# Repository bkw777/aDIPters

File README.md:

# aDIPters
This is a collection of different adapter PCBs to plug SMT parts into DIP sockets, and/or to use a writable part in place of an originally read-only part.
Generally to use a newer PLCC, SOIC, or TSOP EEPROM or Flash part to replace a DIP mask ROM or UV EPROM in a vintage computer.

Most of the PCBs have holes that are intentionally too small to use standard pin headers for the DIP legs.  
Here is how to do the legs: https://gist.github.com/bkw777/52d85d89eeff8445cc667685d05ea94d  
It's less convenient than generic pin headers but the point is for the legs to be as thin as the DIP legs they are emulating so as not to damage sockets, and to have the replacement "chip" be low profile without the big isulator & shoulder block taking up space so the replacement chip fits in more places.  

## 28C256_to_27C256

http://tandy.wiki/28C256_to_27C256

Use an electrically re-programmable EEPROM (28C256) in any socket that normally takes a 256K x 8 UV EPROM (27C256) or standard pinout mask ROM.

The chip may be (re)programmed after soldering by setting the jumpers for programming and placing the board directly in a programmer.

## FlexROM_100

info: http://tandy.wiki/FlexROM_100  

PCB: https://www.pcbway.com/project/shareproject/FlexROM_100.html  
BOM: https://www.digikey.com/short/mmz0bp0h

Uses an electrically re-programmable EEPROM (28C256) in place of the non-standard pinout mask ROM (LH535618) in a TRS-80 Model 100 system rom socket.

Includes /CS signal send-return breakout to use with [REX main rom feature](http://bitchin100.com/wiki/index.php?title=Main_ROM_Management_Feature). This allows not only using the REX main-rom feature but also allows reverting from REX back to the internal main rom without opening the case again to re-install the original main rom chip. It is especially convenient with this [updated PCB for REX Classic](http://tandy.wiki/Building_a_REX), which allows using removable female dupont jumper wires between the FlexROM_100 inside the computer and the REX in the option rom compartment.

To program the eeprom, use either the FlexROM_100_programming_adapter below, or an SOIC-28 test clip.

To install without REX, just install a jumper on the /CS pins.

To use the REX main rom feature:  
* Run 2 10-inch female dupont jumper wires from the /CS pins out to the option-rom compartment.  
* Label the /CS_BUS wire so that you can tell which one it is after the machine is re-assembled.  
* Attach the /CS_BUS wire to TP1 on the REX.  
* Leave the /CS_IC wire un-connected loose in the option rom compartment. Do NOT connect it to TP2. This wire is only used if/when you want to revert from the REX back to the internal main rom without opening the case again.

To re-enable the internal ROM (To remove the REX, or just to stop using the main-rom feature):  
* Disconnect the /CS_BUS wire from the REX TP1 pin.  
* Connect the /CS_BUS wire to the /CS_IC wire with a short male dupont jumper wire.

## FlexROM_100 Programming Adapter

Allows programming the FlexROM_100 without an SOIC-28 test clip.  

## FlashROM_100
Same as FlexROM_100 but using a 29F010 or compatible flash part instead of a 28C256 EEPROM part.  
The board uses a 128K FLASH chip simply because they are what's available these days.  
28C256 have gone from $5 each to $15 each in the last few years.

To program the chip, use the [FlashROM_100_Programming_Adapter](#flashrom_100-programming-adapter) below, and tell the programmer to ignore the size discrepency.  
Example, using a TL-866 and the [minipro](https://gitlab.com/DavidGriffith/minipro) app:  
```
$ minipro -p "SST39SF010A" -u -P -s -w Model_100.y2k.bin
Found TL866II+ 04.2.132 (0x284)
Warning: Firmware is newer than expected.
  Expected  04.2.131 (0x283)
  Found     04.2.132 (0x284)
Chip ID: 0xBFB5  OK
Warning: Incorrect file size: 32768 (needed 131072)
Erasing... 0.40Sec OK
Writing Code...  1.64Sec  OK
Reading Code...  0.25Sec  OK
Verification OK
$
```

TIP: You can run the Model 102 main rom on a Model 100 machine. It fixes a few obscure bugs and there are some tiny differences in the screen font, but otherwise works identically and is compatible with all of the hardware and software.  

There are 2 versions, PLCC and TSOP

### PLCC

https://www.pcbway.com/project/shareproject/FlashROM_100.html

### TSOP

PCB: https://www.pcbway.com/project/shareproject/FlashROM_100_tsop.html  
BOM: https://www.digikey.com/short/7798tt51

## FlashROM_100 Programming Adapter

PCB: https://www.pcbway.com/project/shareproject/Programming_Adapter_for_FlashROM_100.html

Allows re-writing the FlashROM_100.

## FlexROM_102

http://tandy.wiki/FlexROM_102

([DigiKey cart](https://www.digikey.com/en/mylists/list/5FEBN35SNT)) Built 2025.01.15 by John Hutchison KI5NYZ

([OshPark PCB](https://oshpark.com/shared_projects/NmfnbreW)) Built 2025.01.15 by John Hutchison KI5NYZ

This is a cross between the 28C256_to_27C256 above, and the FlexROM_100 above.
This is like FlexROM_100 above but for TANDY 102, 200, and some late-model 100's.

TANDY 102, 200, and some late-model TRS-80 Model 100's have a standard pinout main rom, and so to replace the main rom you can use a plain 27C256, or the generic 28C256_to_27C256 above, or FlexROM_102.  
If a Model 100 has a main rom with part number LH535618, it requires FlexROM_100.  
If a Model 100 has a main rom with part number 3256C07, it requires FlexROM_102 (or 28C256_to_27C256 or an ordinary 27C256).

This just adds pins to break out /CS for use with the main-rom feature of REX Classic, the same as FlexROM_100 above.

The Model 102 system ROM is soldered, so this requires de-soldering the original chip and installing a DIP-28 socket also.

To program the chip, it's like 28C256_to_27C256 above.
Install a jumper on the /CS pins, set the mini jumpers to PROGRAM (two shunts on the two pairs of pins), put the board directly in the programmer, and set the programmer for 28C256.  
There is no separate programming adapter needed like for FlexROM_100 and FlashROM_100.

To install/run, install a jumper on the /CS pins, set the mini jumpers to RUN (single shunt on the two center pins), and install the board in the Model 102 in place of the main rom.

There is a jumper on the /CS pins in both cases. The only time there is not a jumper on the /CS pins is to use the REX Classic main-rom feature.  
See the FlexROM_100 directions for that.

Some late-model TRS-80 Model 100\'s  

## FlexROM_200_M13
THIS ONE IS UNTESTED  
Replaces the 8K ROM at position M13 in TANDY 200

[FlexROM_200_M13 BOM](FlexROM_200_M13.BOM.csv) or ([DigiKey cart](https://www.digikey.com/short/q3zm9cf4))  
http://tandy.wiki/FlexROM_200

## FLASH_23C1000

http://tandy.wiki/FLASH_23C1000  
https://www.pcbway.com/project/shareproject/FlashROM_8300.html

Replaces 23C1000, uPD23C1000, D23C1000A, MX23C1000, etc.

This board accepts a variety of writable flash, eeprom, or eprom devices to replace the non-standard pinout 23C1000.
Tested on NEC PC-8300, PC-8401 Starlet, and PC-8500. Not tested but should also work in Cambridge Z88, or anywhere a 23C1000 is used.

The nominal flash chip is SST39SF010, but there are several other compatible parts. The specs for a compatible chip are:
* 128K x 8  
* 5v  
* parallel  
* 7x9pin PLCC32, or 8x14mm sTSOP32, or 8x20mm TSOP32  

It also supports EPROM and EEPROM parts as well as flash parts.  
At least the following parts are compatible:  
* 29F010  
* 39SF010  
* 29SF010  
* 29EE010  
* 28C010  
* 28F010  
* 27SF010  
* 27C010  

The R3 resistor is only needed for EPROM and EEPROM devices that have a Vpp pin (27xxx/28xxx). Flash devices (29xxx) don't use it.

The RUN/PRG jumper alters the pinout, so that the chip may be programmed by placing the board directly in a programmer.

For programming:  
1. Place the jumper in the PRG position  
1. Place the board in the programmer  

For installing in place of the 23C1000:  
1. Place the jumper in the RUN position  
1. Place the board in the socket with the top 4 pins (1, 2, 31, 32) hanging off the pin #1 end of the socket, and the bottom 28 pins 3-30 filling the socket. Board pin 3 ends up in socket pin 1.

For NEC PC-8401, cut pin 1 a little short so that it doesn't touch R65, or use the DIP-28 version of this board below instead of this DIP-32 version.

For safety, cut all 4 top pins a little short, 1, 2, 31, 32, so that they don't risk touching the motherboard.  
These pins are only used for programming. They only need to be long enough for the programmer socket to grab them for a few seconds.

## FLASH_23C1000_DIP28

http://tandy.wiki/FLASH_23C1000  
https://www.pcbway.com/project/shareproject/FLASH_23C1000_DIP28.html

Replaces 23C1000, uPD23C1000, D23C1000A, MX23C1000, etc.

Same as FLASH_23C1000, except:
* Does not exceed the original parts DIP-28 footprint.  
* Does not accept 27C010 or other parts that have a Vpp pin.  
* Does accept 256k *020 parts.  

Tested in NEC PC-8300, PC-8401, PC-8500  
Not yet tested but should also work in Cambridge Z88

Programming this version is slightly more complicated.

To program:  
* Place the board in the programmer 2 rows from the top, such that pin 1 on the board is in pin 3 of an imaginary DIP-32 in the programmer.
* Remove the VCC-/WE jumper.
* Move the /OE-A16 jumper to /OE
* Connect the A16 pin to programmer DIP-32 pin 2 using a female-to-male dupont jumper wire
* Connect the VCC pin to programmer DIP-32 pin 32
* Connect the /WE pin to programmer DIP-32 pin 31

Configure the programmer for whatever device is installed on the board, IE SST39SF010A etc.

To install:  
* Install a jumper across the VCC-/WE pins
* Move the /OE-A16 jumper to A16
* Install the board in the DIP-28 socket in place of any uPD23C1000, D23C1000A, MX23C1000 etc.

## TANDY 100/102/200 Option ROM to 27C256 pinout programming adapter

If you have a Molex 8878-28S socket, this provides a pinout adapter for the non-standard TANDY pinout to a standard 27C256 pinout to allow reading Model 100/200 Option ROMs in an eprom programmer without having to bend the pins or desolder the chip.  
The sockets haven't been made for decades, but sometimes they turn up on [ebay](ebay.com/sch/?_nkw=molex%208878-28S) and other places.  
Search terms: The socket is physically marked "Molex 8878-28S".  
The [datasheet](datasheets/015299282_sd_corrected.pdf) says the part number is 78805-0518 or 15-29-9282.  

The jumpers provide 5 different ways to handle pin #23 in the socket.  

In the Model 100 option rom socket, pin 23 is connected to the ALE bus signal and labelled as a 2nd active-low /CE.  
To make the Molex socket on the adapter emulate the option rom socket in a Model 100 as completely as possible, pin 23 in the socket should be a 2nd copy of the /CE pin from the programmer. Basically using the /CE signal as a fake ALE signal.  
But only 2 known option roms actually use the signal, MS MultiPLAN and Interactive Solutions.  
Most commercial option roms are a 27C256 in some form of pinout adapter, and they don't connect the ALE pin from the bus to anything.  

The jumpers allow pin 23 in the Molex socket to be connected to the programmer pins: GND, VCC, VPP, /CE, or nothing.  
* For the molded plastic roms with LH53562x part numbers (MS MultiPLAN, Ineractive Solutions), use the /CE position.  
* For most 3rd party roms constructed of a ceramic 27C256 with a pinout adapter, use either /CE, or remove the jumper entirely.  
* The other options are for possible future use with other new custom option rom modules like [Teeprom](httpsgithub.com/bkw777/Teeprom) or [M4ROM](https://github.com/bkw777/M4ROM/) etc, that might be specifically designed to use that otherwise un-used pin for VPP or /WE etc. Currently no such modules are wired like that, so generally just leave it on /CE.

## DS1000

## SM8 SSOP-8 DIP-8

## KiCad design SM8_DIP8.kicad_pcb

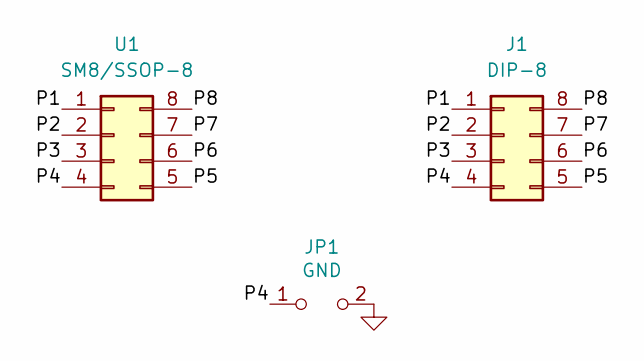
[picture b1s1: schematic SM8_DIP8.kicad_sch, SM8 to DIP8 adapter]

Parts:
J1: DIP-8; DIP8_0.3_pcb_sil_pins
JP1: GND; SolderJumper-2_P1.3mm_Open_RoundedPad1.0x1.5mm
U1: SM8/SSOP-8; SSOP-8_2.95x2.8x0.65

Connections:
/P1: J1.1, U1.1
/P2: J1.2, U1.2
/P3: J1.3, U1.3
/P4: J1.4, JP1.1 (A), U1.4
/P5: J1.5, U1.5
/P6: J1.6, U1.6
/P7: J1.7, U1.7
/P8: J1.8, U1.8
GND: JP1.2 (B)

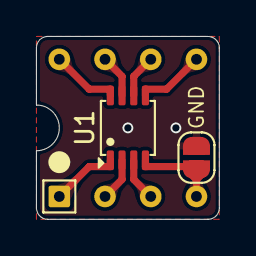
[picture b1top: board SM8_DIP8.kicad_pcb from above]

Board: 2 copper layers, 10.2 x 10.2 mm, 3 parts (0 on the bottom side), 8 nets.

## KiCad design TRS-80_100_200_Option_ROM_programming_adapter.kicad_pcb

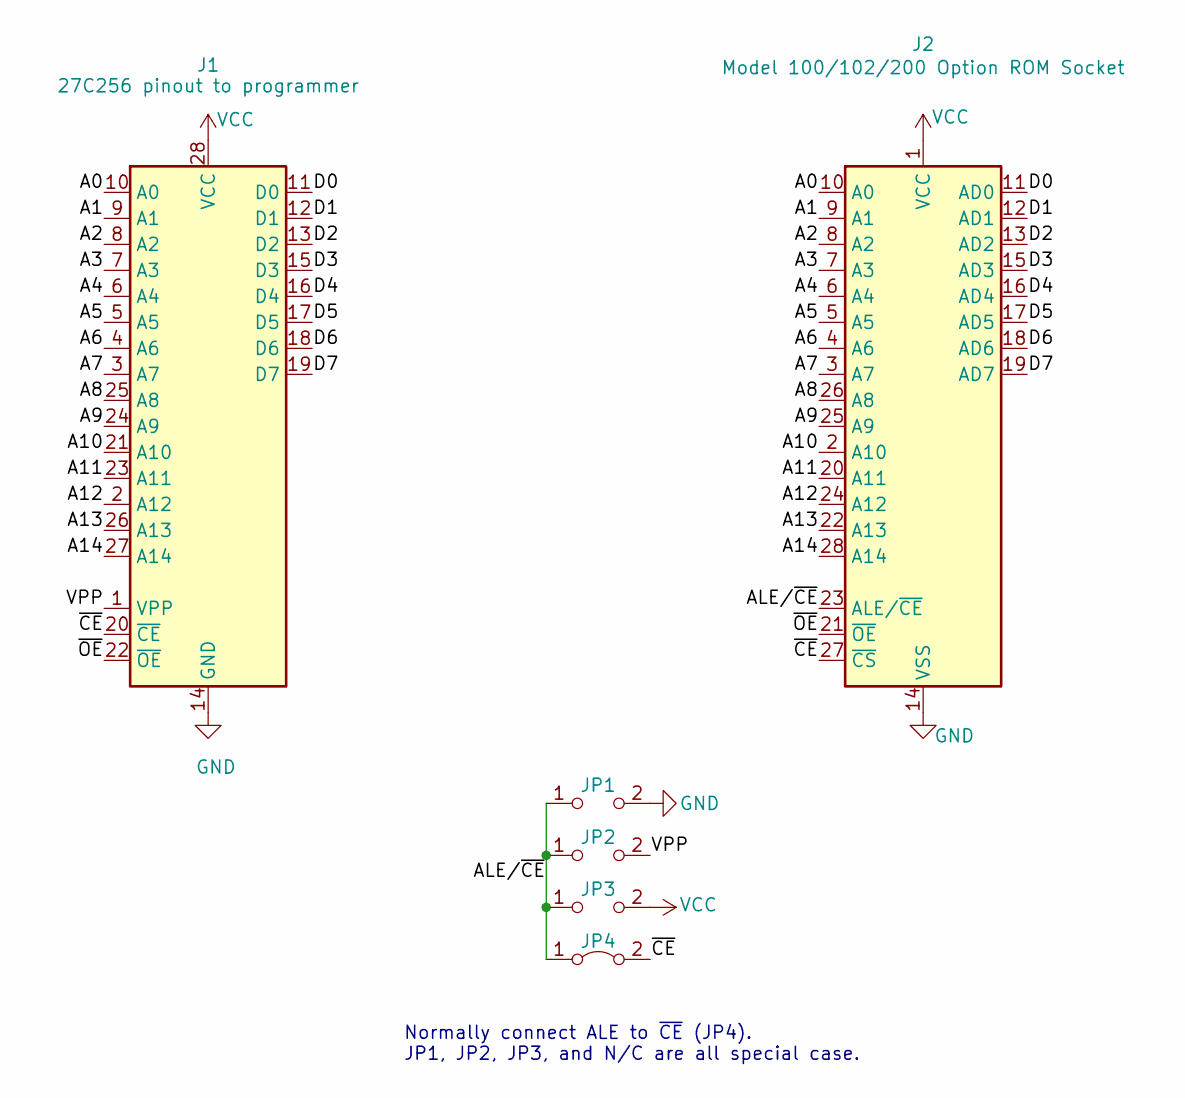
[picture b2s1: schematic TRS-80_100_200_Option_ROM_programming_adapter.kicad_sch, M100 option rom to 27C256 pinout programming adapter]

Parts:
J1: 27C256 pinout to programmer; 2x28_0.3_0.1_pins
J2: Model 100/102/200 Option ROM Socket; Molex_78805
JP1: GND; PinHeader_1x02_P2.54mm_Vertical
JP2: VPP; PinHeader_1x02_P2.54mm_Vertical
JP3: VCC; PinHeader_1x02_P2.54mm_Vertical
JP4: ~{CE}; PinHeader_1x02_P2.54mm_Vertical_shorted

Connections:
/A0: J1.10 (A0), J2.10 (A0)
/A1: J1.9 (A1), J2.9 (A1)
/A2: J1.8 (A2), J2.8 (A2)
/A3: J1.7 (A3), J2.7 (A3)
/A4: J1.6 (A4), J2.6 (A4)
/A5: J1.5 (A5), J2.5 (A5)
/A6: J1.4 (A6), J2.4 (A6)
/A7: J1.3 (A7), J2.3 (A7)
/A8: J1.25 (A8), J2.26 (A8)
/A9: J1.24 (A9), J2.25 (A9)
/A10: J1.21 (A10), J2.2 (A10)
/A11: J1.23 (A11), J2.20 (A11)
/A12: J1.2 (A12), J2.24 (A12)
/A13: J1.26 (A13), J2.22 (A13)
/A14: J1.27 (A14), J2.28 (A14)
/ALE/~CE: J2.23 (ALE/~CE), JP1.1 (A), JP2.1 (A), JP3.1 (A), JP4.1 (A)
/D0: J1.11 (D0), J2.11 (AD0)
/D1: J1.12 (D1), J2.12 (AD1)
/D2: J1.13 (D2), J2.13 (AD2)
/D3: J1.15 (D3), J2.15 (AD3)
/D4: J1.16 (D4), J2.16 (AD4)
/D5: J1.17 (D5), J2.17 (AD5)
/D6: J1.18 (D6), J2.18 (AD6)
/D7: J1.19 (D7), J2.19 (AD7)
/VPP: J1.1 (VPP), JP2.2 (B)
/~CE: J1.20 (~CE), J2.27 (~CS), JP4.2 (B)
/~OE: J1.22 (~OE), J2.21 (~OE)
GND: J1.14 (GND), J2.14 (VSS), JP1.2 (B)
VCC: J1.28 (VCC), J2.1 (VCC), JP3.2 (B)

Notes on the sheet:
Normally connect ALE to ~{CE} (JP4). JP1, JP2, JP3, and N/C are all special case.

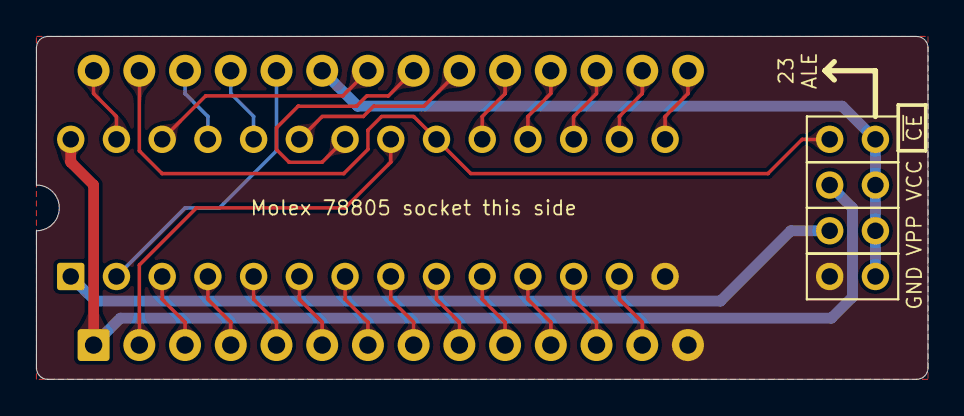
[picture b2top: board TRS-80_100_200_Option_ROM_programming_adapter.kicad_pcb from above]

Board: 2 copper layers, 49.5 x 19.1 mm, 6 parts (0 on the bottom side), 29 nets.

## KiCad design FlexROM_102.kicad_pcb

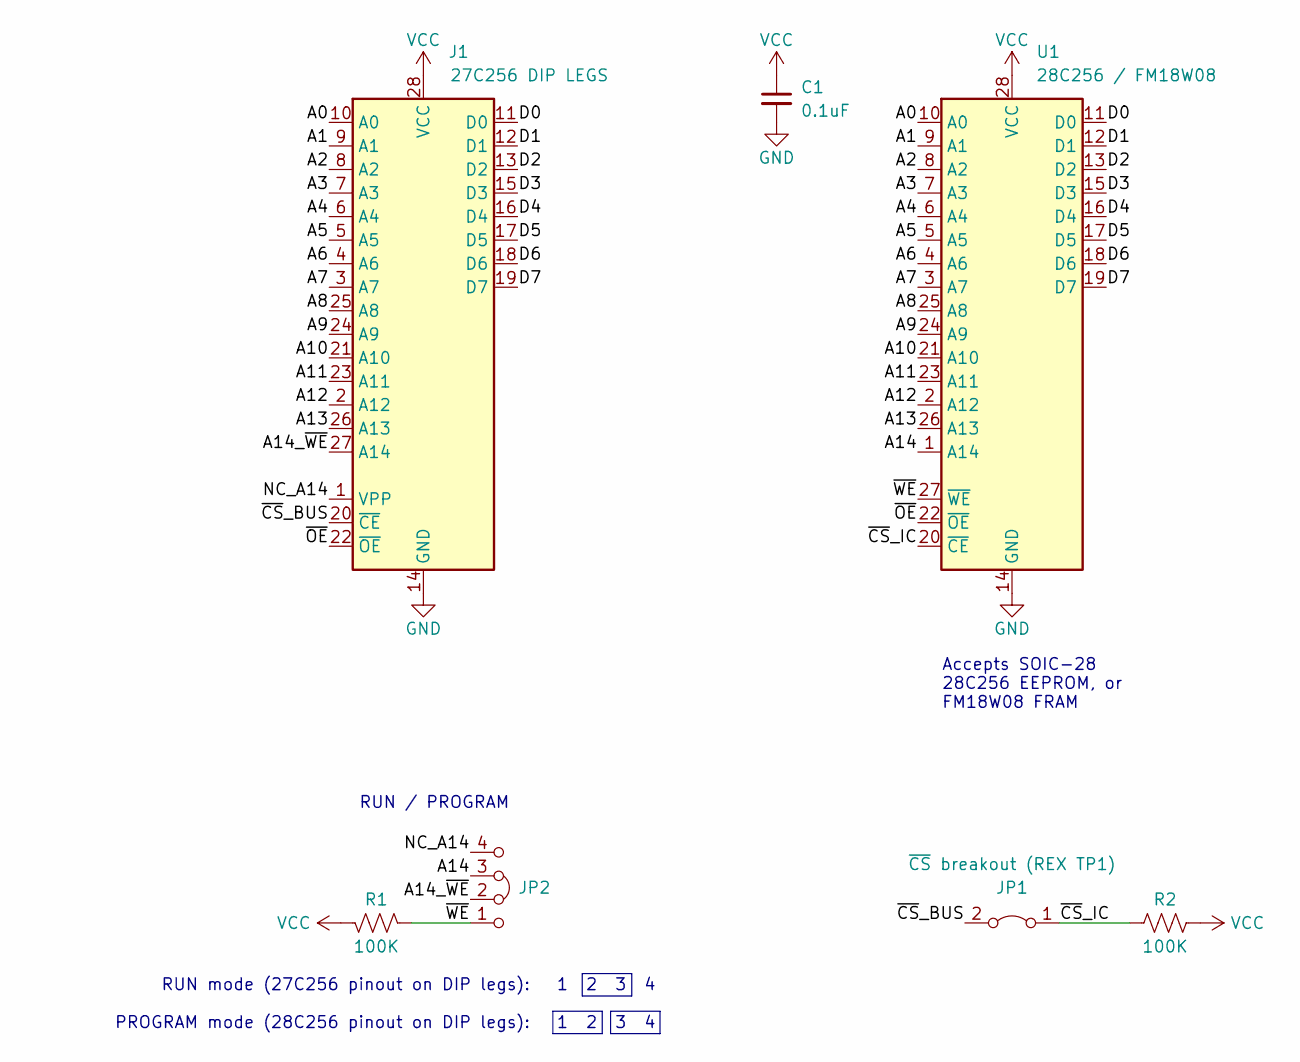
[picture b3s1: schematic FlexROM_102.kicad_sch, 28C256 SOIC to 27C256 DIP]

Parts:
C1: 0.1uF; C_0805
J1: 27C256 DIP LEGS; DIP28_0.6_pcb
JP1: ~{CS} breakout (REX TP1); Pin_Header_Angled_1x02_Pitch2.54mm
JP2: Jumper_4_Bridged23; PinHeader_1x04_P2.00mm_Horizontal
R1, R2: 100K; R_0805
U1: 28C256 / FM18W08; SOIC28W

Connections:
/A0: J1.10 (A0), U1.10 (A0)
/A1: J1.9 (A1), U1.9 (A1)
/A2: J1.8 (A2), U1.8 (A2)
/A3: J1.7 (A3), U1.7 (A3)
/A4: J1.6 (A4), U1.6 (A4)
/A5: J1.5 (A5), U1.5 (A5)
/A6: J1.4 (A6), U1.4 (A6)
/A7: J1.3 (A7), U1.3 (A7)
/A8: J1.25 (A8), U1.25 (A8)
/A9: J1.24 (A9), U1.24 (A9)
/A10: J1.21 (A10), U1.21 (A10)
/A11: J1.23 (A11), U1.23 (A11)
/A12: J1.2 (A12), U1.2 (A12)
/A13: J1.26 (A13), U1.26 (A13)
/A14: JP2.3 (C), U1.1 (A14)
/A14_~WE: J1.27 (A14), JP2.2 (B)
/D0: J1.11 (D0), U1.11 (D0)
/D1: J1.12 (D1), U1.12 (D1)
/D2: J1.13 (D2), U1.13 (D2)
/D3: J1.15 (D3), U1.15 (D3)
/D4: J1.16 (D4), U1.16 (D4)
/D5: J1.17 (D5), U1.17 (D5)
/D6: J1.18 (D6), U1.18 (D6)
/D7: J1.19 (D7), U1.19 (D7)
/NC_A14: J1.1 (VPP), JP2.4 (D)
/~CS_BUS: J1.20 (~CE), JP1.2 (B)
/~CS_IC: JP1.1 (A), R2.1, U1.20 (~CE)
/~OE: J1.22 (~OE), U1.22 (~OE)
/~WE: JP2.1 (A), R1.2, U1.27 (~WE)
GND: C1.2, J1.14 (GND), U1.14 (GND)
VCC: C1.1, J1.28 (VCC), R1.1, R2.2, U1.28 (VCC)

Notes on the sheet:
Accepts SOIC-28 28C256 EEPROM, or FM18W08 FRAM
RUN / PROGRAM
RUN mode (27C256 pinout on DIP legs): 1 2 3 4 PROGRAM mode (28C256 pinout on DIP legs): 1 2 3 4

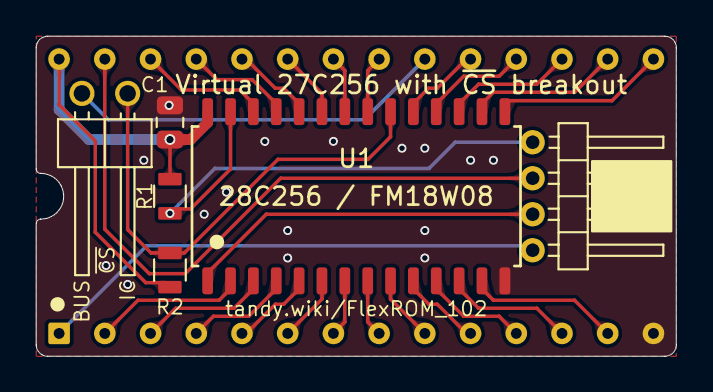
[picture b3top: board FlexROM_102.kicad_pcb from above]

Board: 2 copper layers, 35.6 x 17.8 mm, 7 parts (0 on the bottom side), 31 nets.

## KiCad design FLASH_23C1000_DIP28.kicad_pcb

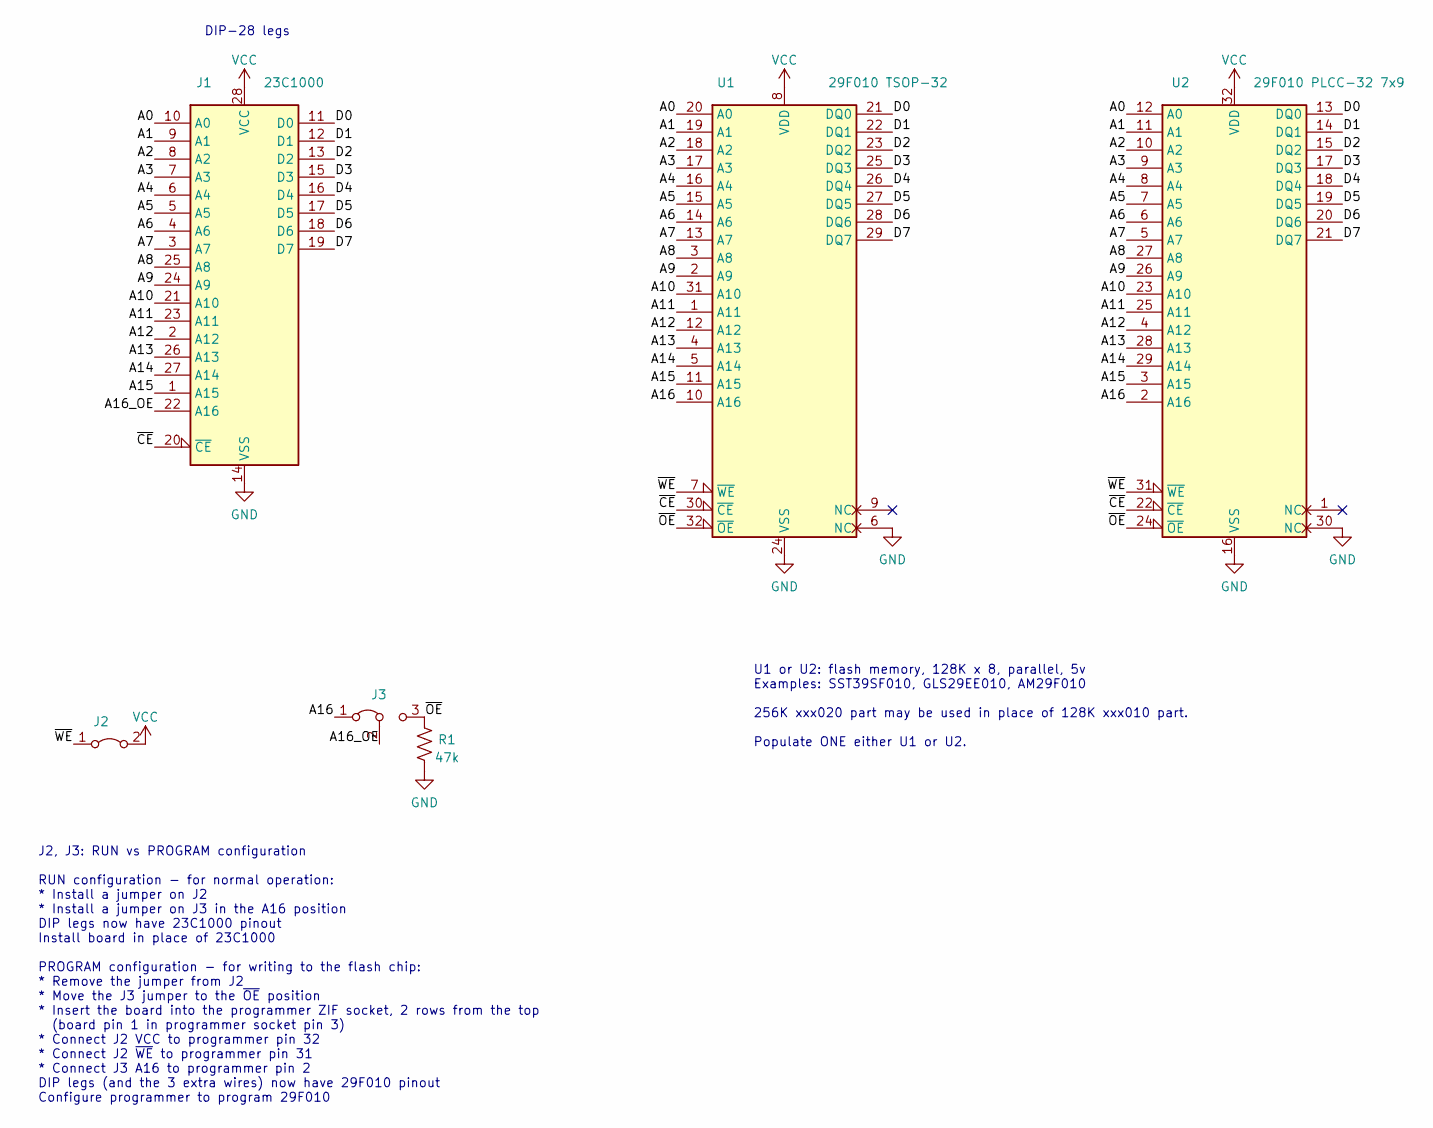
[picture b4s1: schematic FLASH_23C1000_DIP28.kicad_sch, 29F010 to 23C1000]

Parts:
J1: 23C1000; DIP-28_600_pcb_shallow_notch
J2: Conn_1x2; Pin_Header_Angled_1x02_Pitch2.54mm_shorted
J3: Conn_1x3; Pin_Header_Angled_1x03_Pitch2.54mm_12shorted
R1: 47k; R_0805
U1: 29F010 TSOP-32; TSOP32-dual
U2: 29F010 PLCC-32 7x9; PLCC32_7x9

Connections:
/A0: J1.10 (A0), U1.20 (A0), U2.12 (A0)
/A1: J1.9 (A1), U1.19 (A1), U2.11 (A1)
/A2: J1.8 (A2), U1.18 (A2), U2.10 (A2)
/A3: J1.7 (A3), U1.17 (A3), U2.9 (A3)
/A4: J1.6 (A4), U1.16 (A4), U2.8 (A4)
/A5: J1.5 (A5), U1.15 (A5), U2.7 (A5)
/A6: J1.4 (A6), U1.14 (A6), U2.6 (A6)
/A7: J1.3 (A7), U1.13 (A7), U2.5 (A7)
/A8: J1.25 (A8), U1.3 (A8), U2.27 (A8)
/A9: J1.24 (A9), U1.2 (A9), U2.26 (A9)
/A10: J1.21 (A10), U1.31 (A10), U2.23 (A10)
/A11: J1.23 (A11), U1.1 (A11), U2.25 (A11)
/A12: J1.2 (A12), U1.12 (A12), U2.4 (A12)
/A13: J1.26 (A13), U1.4 (A13), U2.28 (A13)
/A14: J1.27 (A14), U1.5 (A14), U2.29 (A14)
/A15: J1.1 (A15), U1.11 (A15), U2.3 (A15)
/A16: J3.1 (A), U1.10 (A16), U2.2 (A16)
/A16_OE: J1.22 (A16), J3.2 (C)
/D0: J1.11 (D0), U1.21 (DQ0), U2.13 (DQ0)
/D1: J1.12 (D1), U1.22 (DQ1), U2.14 (DQ1)
/D2: J1.13 (D2), U1.23 (DQ2), U2.15 (DQ2)
/D3: J1.15 (D3), U1.25 (DQ3), U2.17 (DQ3)
/D4: J1.16 (D4), U1.26 (DQ4), U2.18 (DQ4)
/D5: J1.17 (D5), U1.27 (DQ5), U2.19 (DQ5)
/D6: J1.18 (D6), U1.28 (DQ6), U2.20 (DQ6)
/D7: J1.19 (D7), U1.29 (DQ7), U2.21 (DQ7)
/~CE: J1.20 (~CE), U1.30 (~CE), U2.22 (~CE)
/~OE: J3.3 (B), R1.1, U1.32 (~OE), U2.24 (~OE)
/~WE: J2.1 (A), U1.7 (~WE), U2.31 (~WE)
GND: J1.14 (VSS), R1.2, U1.6 (NC), U1.24 (VSS), U2.16 (VSS), U2.30 (NC)
VCC: J1.28 (VCC), J2.2 (B), U1.8 (VDD), U2.32 (VDD)

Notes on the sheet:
DIP-28 legs
U1 or U2: flash memory, 128K x 8, parallel, 5v Examples: SST39SF010, GLS29EE010, AM29F010 256K xxx020 part may be used in place of 128K xxx010 part. Populate ONE either U1 or U2.
J2, J3: RUN vs PROGRAM configuration RUN configuration - for normal operation: * Install a jumper on J2 * Install a jumper on J3 in the A16 position DIP legs now have 23C1000 pinout Install board in place of 23C1000 PROGRAM configuration - for writing to the flash chip: * Remove the jumper from J2 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

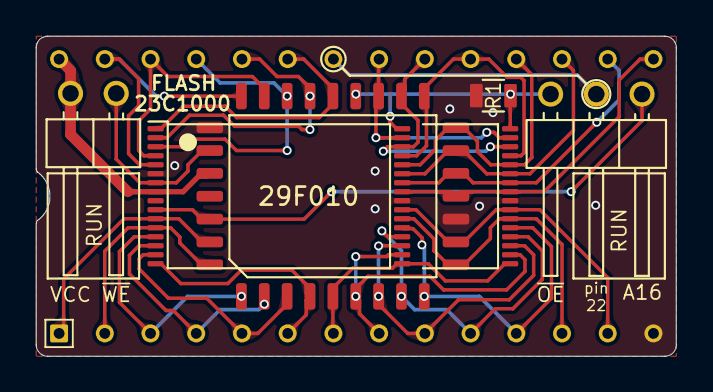
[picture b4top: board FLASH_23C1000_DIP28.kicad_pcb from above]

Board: 2 copper layers, 35.6 x 17.8 mm, 6 parts (0 on the bottom side), 31 nets.

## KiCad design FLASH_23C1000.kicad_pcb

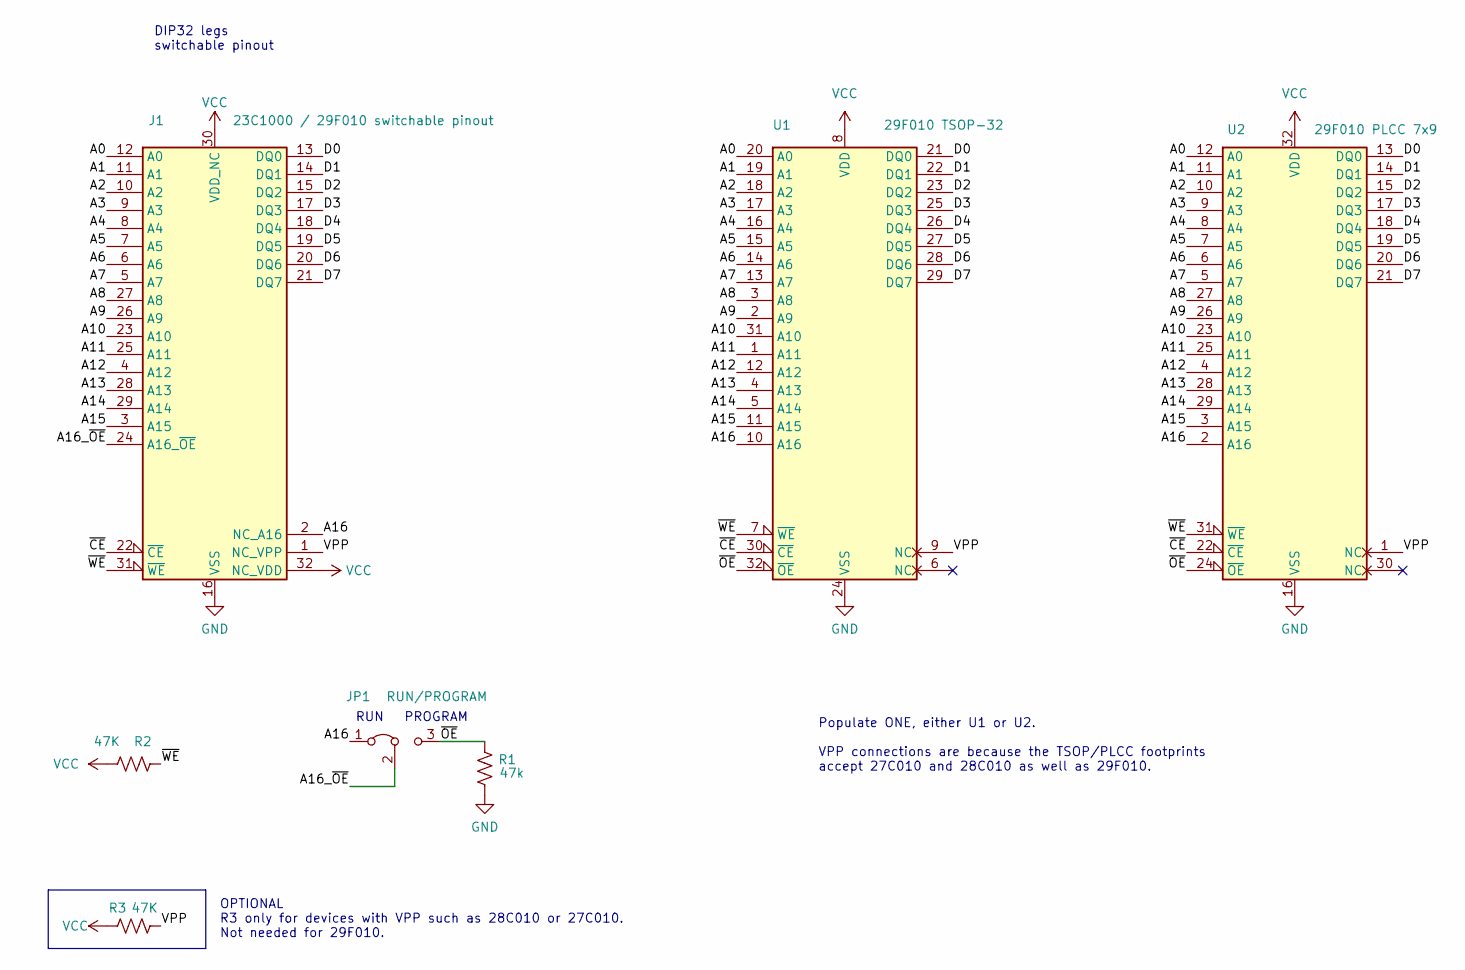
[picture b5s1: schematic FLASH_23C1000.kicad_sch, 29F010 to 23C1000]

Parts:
J1: 23C1000 / 29F010 switchable pinout; DIP32_DIP28_0.6_pcb_sil_pins
JP1: RUN/PROGRAM; Pin_Header_Angled_1x03_Pitch2.54mm_12shorted
R1: 47k; R_0805
R2, R3: 47K; R_0805
U1: 29F010 TSOP-32; TSOP32-dual
U2: 29F010 PLCC 7x9; PLCC32_7x9

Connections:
/A0: J1.12 (A0), U1.20 (A0), U2.12 (A0)
/A1: J1.11 (A1), U1.19 (A1), U2.11 (A1)
/A2: J1.10 (A2), U1.18 (A2), U2.10 (A2)
/A3: J1.9 (A3), U1.17 (A3), U2.9 (A3)
/A4: J1.8 (A4), U1.16 (A4), U2.8 (A4)
/A5: J1.7 (A5), U1.15 (A5), U2.7 (A5)
/A6: J1.6 (A6), U1.14 (A6), U2.6 (A6)
/A7: J1.5 (A7), U1.13 (A7), U2.5 (A7)
/A8: J1.27 (A8), U1.3 (A8), U2.27 (A8)
/A9: J1.26 (A9), U1.2 (A9), U2.26 (A9)
/A10: J1.23 (A10), U1.31 (A10), U2.23 (A10)
/A11: J1.25 (A11), U1.1 (A11), U2.25 (A11)
/A12: J1.4 (A12), U1.12 (A12), U2.4 (A12)
/A13: J1.28 (A13), U1.4 (A13), U2.28 (A13)
/A14: J1.29 (A14), U1.5 (A14), U2.29 (A14)
/A15: J1.3 (A15), U1.11 (A15), U2.3 (A15)
/A16: J1.2 (NC_A16), JP1.1 (A), U1.10 (A16), U2.2 (A16)
/A16_~OE: J1.24 (A16_~OE), JP1.2 (C)
/D0: J1.13 (DQ0), U1.21 (DQ0), U2.13 (DQ0)
/D1: J1.14 (DQ1), U1.22 (DQ1), U2.14 (DQ1)
/D2: J1.15 (DQ2), U1.23 (DQ2), U2.15 (DQ2)
/D3: J1.17 (DQ3), U1.25 (DQ3), U2.17 (DQ3)
/D4: J1.18 (DQ4), U1.26 (DQ4), U2.18 (DQ4)
/D5: J1.19 (DQ5), U1.27 (DQ5), U2.19 (DQ5)
/D6: J1.20 (DQ6), U1.28 (DQ6), U2.20 (DQ6)
/D7: J1.21 (DQ7), U1.29 (DQ7), U2.21 (DQ7)
/VPP: J1.1 (NC_VPP), R3.1, U1.9 (NC), U2.1 (NC)
/~CE: J1.22 (~CE), U1.30 (~CE), U2.22 (~CE)
/~OE: JP1.3 (B), R1.1, U1.32 (~OE), U2.24 (~OE)
/~WE: J1.31 (~WE), R2.1, U1.7 (~WE), U2.31 (~WE)
GND: J1.16 (VSS), R1.2, U1.24 (VSS), U2.16 (VSS)
VCC: J1.30 (VDD_NC), J1.32 (NC_VDD), R2.2, R3.2, U1.8 (VDD), U2.32 (VDD)

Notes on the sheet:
Populate ONE, either U1 or U2. VPP connections are because the TSOP/PLCC footprints accept 27C010 and 28C010 as well as 29F010.
RUN
OPTIONAL R3 only for devices with VPP such as 28C010 or 27C010. Not needed for 29F010.
DIP32 legs switchable pinout
PROGRAM

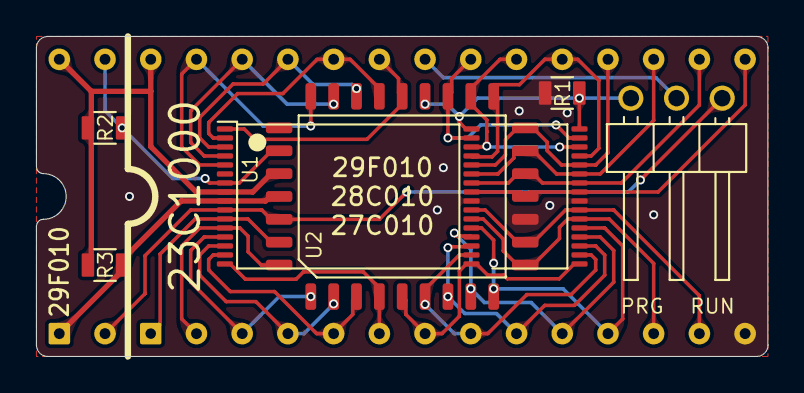
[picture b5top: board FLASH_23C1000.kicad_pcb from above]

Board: 2 copper layers, 40.6 x 17.8 mm, 7 parts (0 on the bottom side), 32 nets.

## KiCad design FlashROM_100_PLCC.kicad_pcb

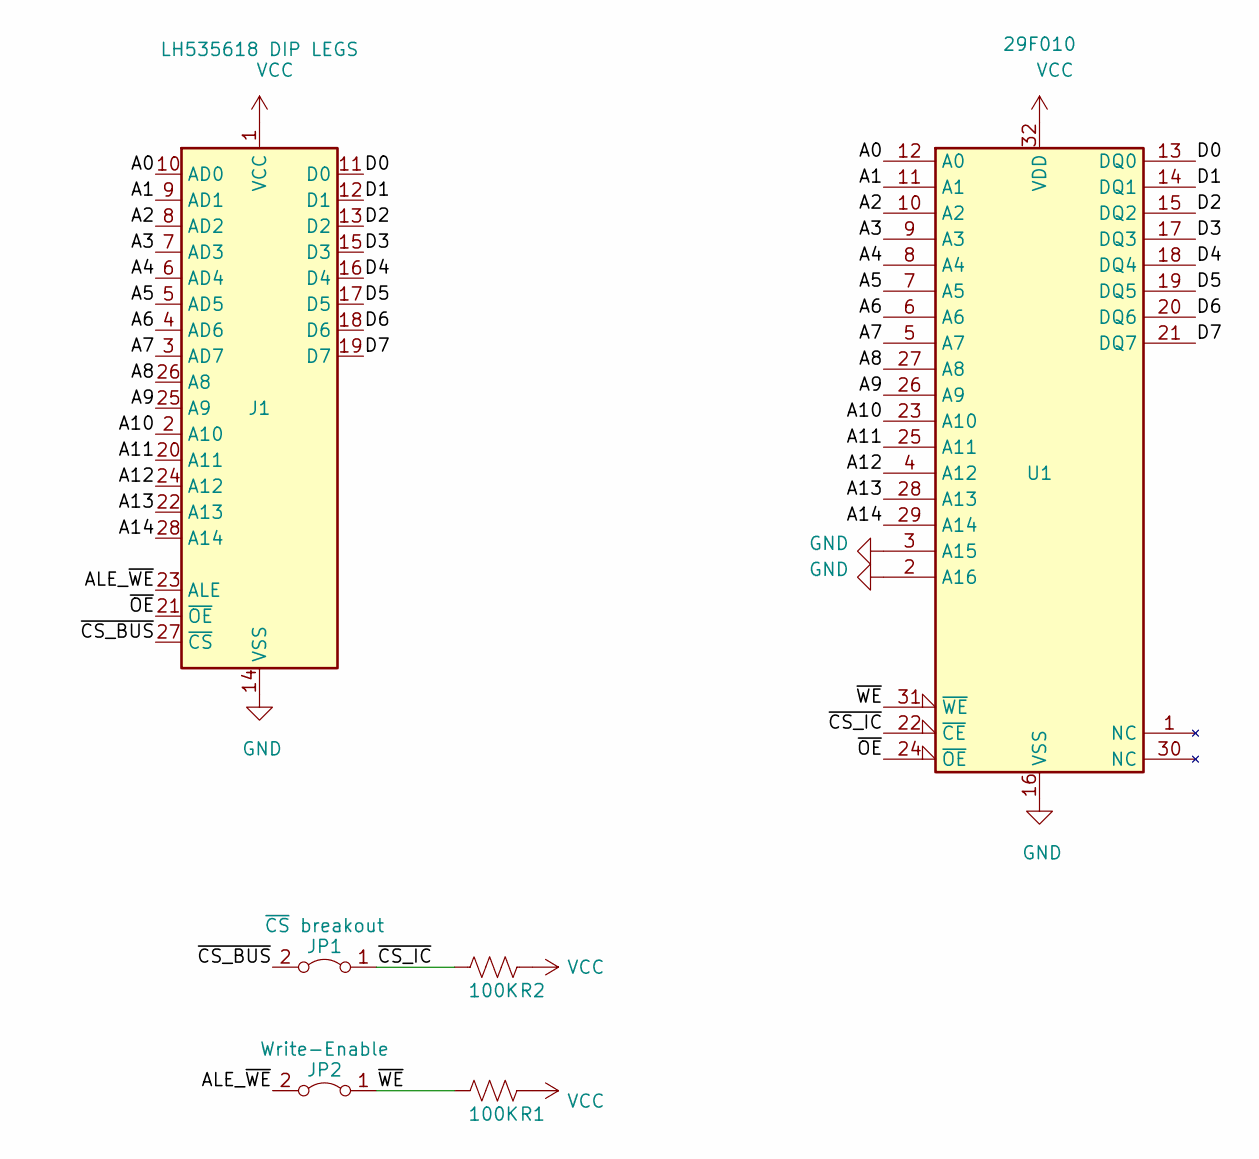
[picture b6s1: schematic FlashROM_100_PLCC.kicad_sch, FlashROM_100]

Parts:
J1: LH535618 DIP LEGS; DIP28_0.6_pcb
JP1: ~{CS} breakout; Pin_Header_Angled_1x02_Pitch2.54mm
JP2: Write-Enable; Pin_Header_Angled_1x02_Pitch2.54mm
R1, R2: 100K; R_0805
U1: 29F010; PLCC32_7x9

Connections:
/A0: J1.10 (AD0), U1.12 (A0)
/A1: J1.9 (AD1), U1.11 (A1)
/A2: J1.8 (AD2), U1.10 (A2)
/A3: J1.7 (AD3), U1.9 (A3)
/A4: J1.6 (AD4), U1.8 (A4)
/A5: J1.5 (AD5), U1.7 (A5)
/A6: J1.4 (AD6), U1.6 (A6)
/A7: J1.3 (AD7), U1.5 (A7)
/A8: J1.26 (A8), U1.27 (A8)
/A9: J1.25 (A9), U1.26 (A9)
/A10: J1.2 (A10), U1.23 (A10)
/A11: J1.20 (A11), U1.25 (A11)
/A12: J1.24 (A12), U1.4 (A12)
/A13: J1.22 (A13), U1.28 (A13)
/A14: J1.28 (A14), U1.29 (A14)
/ALE_~WE: J1.23 (ALE), JP2.2 (B)
/D0: J1.11 (D0), U1.13 (DQ0)
/D1: J1.12 (D1), U1.14 (DQ1)
/D2: J1.13 (D2), U1.15 (DQ2)
/D3: J1.15 (D3), U1.17 (DQ3)
/D4: J1.16 (D4), U1.18 (DQ4)
/D5: J1.17 (D5), U1.19 (DQ5)
/D6: J1.18 (D6), U1.20 (DQ6)
/D7: J1.19 (D7), U1.21 (DQ7)
/~CS_BUS: J1.27 (~CS), JP1.2 (B)
/~CS_IC: JP1.1 (A), R2.1, U1.22 (~CE)
/~OE: J1.21 (~OE), U1.24 (~OE)
/~WE: JP2.1 (A), R1.1, U1.31 (~WE)
GND: J1.14 (VSS), U1.2 (A16), U1.3 (A15), U1.16 (VSS)
VCC: J1.1 (VCC), R1.2, R2.2, U1.32 (VDD)

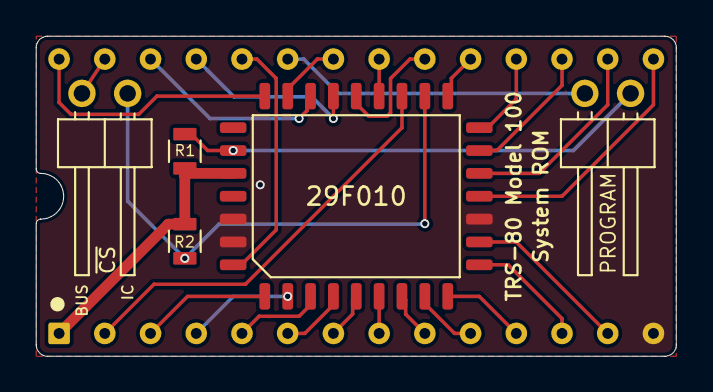
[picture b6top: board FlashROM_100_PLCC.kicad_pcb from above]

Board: 2 copper layers, 35.6 x 17.8 mm, 6 parts (0 on the bottom side), 30 nets.

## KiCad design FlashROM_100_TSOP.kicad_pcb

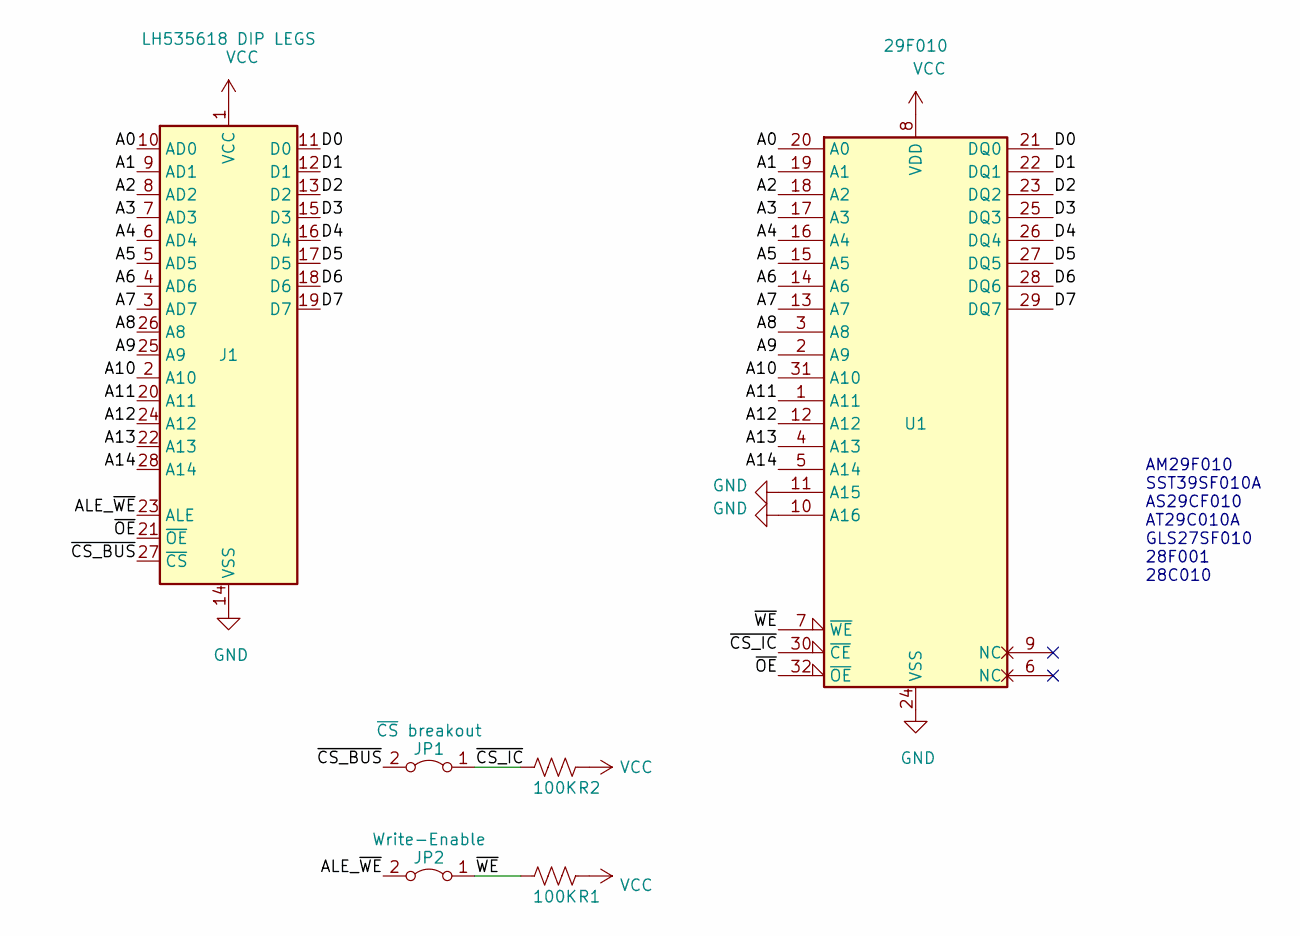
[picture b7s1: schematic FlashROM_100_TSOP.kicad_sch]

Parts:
J1: LH535618 DIP LEGS; DIP28_0.6_pcb
JP1: ~{CS} breakout; Pin_Header_Angled_1x02_Pitch2.54mm
JP2: Write-Enable; Pin_Header_Angled_1x02_Pitch2.54mm
R1, R2: 100K; R_0805
U1: 29F010; TSOP32-dual

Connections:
/A0: J1.10 (AD0), U1.20 (A0)
/A1: J1.9 (AD1), U1.19 (A1)
/A2: J1.8 (AD2), U1.18 (A2)
/A3: J1.7 (AD3), U1.17 (A3)
/A4: J1.6 (AD4), U1.16 (A4)
/A5: J1.5 (AD5), U1.15 (A5)
/A6: J1.4 (AD6), U1.14 (A6)
/A7: J1.3 (AD7), U1.13 (A7)
/A8: J1.26 (A8), U1.3 (A8)
/A9: J1.25 (A9), U1.2 (A9)
/A10: J1.2 (A10), U1.31 (A10)
/A11: J1.20 (A11), U1.1 (A11)
/A12: J1.24 (A12), U1.12 (A12)
/A13: J1.22 (A13), U1.4 (A13)
/A14: J1.28 (A14), U1.5 (A14)
/ALE_~WE: J1.23 (ALE), JP2.2 (B)
/D0: J1.11 (D0), U1.21 (DQ0)
/D1: J1.12 (D1), U1.22 (DQ1)
/D2: J1.13 (D2), U1.23 (DQ2)
/D3: J1.15 (D3), U1.25 (DQ3)
/D4: J1.16 (D4), U1.26 (DQ4)
/D5: J1.17 (D5), U1.27 (DQ5)
/D6: J1.18 (D6), U1.28 (DQ6)
/D7: J1.19 (D7), U1.29 (DQ7)
/~CS_BUS: J1.27 (~CS), JP1.2 (B)
/~CS_IC: JP1.1 (A), R2.1, U1.30 (~CE)
/~OE: J1.21 (~OE), U1.32 (~OE)
/~WE: JP2.1 (A), R1.1, U1.7 (~WE)
GND: J1.14 (VSS), U1.10 (A16), U1.11 (A15), U1.24 (VSS)
VCC: J1.1 (VCC), R1.2, R2.2, U1.8 (VDD)

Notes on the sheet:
AM29F010 SST39SF010A AS29CF010 AT29C010A GLS27SF010 28F001 28C010

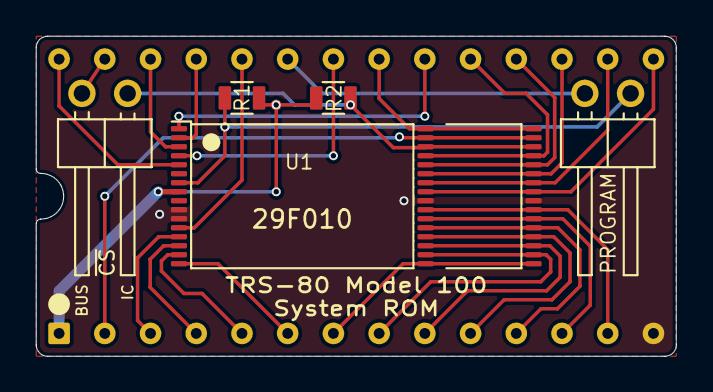
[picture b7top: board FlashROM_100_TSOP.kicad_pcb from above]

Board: 2 copper layers, 35.6 x 17.8 mm, 6 parts (0 on the bottom side), 30 nets.

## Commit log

2020-03-05 Update LICENSE
2020-03-06 initial commit, uPD23C1000_FLASH, 27C256_28C256
2020-03-07 27C256_28C256: add jumpers to allow programming without needing a test clip
2020-03-08 pours and text
2020-03-08 improve copper pour
2020-03-10 Add FlexROM_100, FlexROM_102
2020-03-11 Add 32-pin version of FlashROM_8300. Doesn't need any jumper wires to program.
2020-03-11 footprint name changed
2020-03-14 readme and silkscreen
2020-03-14 silkscreen
2020-03-14 depreciate DIP28 version of FlashROM_8300, and 29EE010 chips
2020-03-14 project page link for 27C256_28C256
2020-03-14 docs for FlashROM_8300, add VPP & pullup on FlashROM_8300 to support old flash, eeprom, & eprom devices.
2020-03-22 silkscreen & 3d view
2020-03-22 readme, compatible chips for FlashROM_8300
2020-03-22 FlashROM_8300 silkscreen
2020-03-22 typo
2020-10-26 FlashROM_8300: tsop footprints, zone fills
2020-11-02 FlexROM_100 programming adapter, FlexROM_102 programming jumpers
2020-11-03 minor tidying
2020-11-04 upD23C1000 add A17 & R2
2020-11-04 uPD23C1000 & FlashROM_8300 correct A17 & A18 handling
2020-11-05 Add FlashROM_100. /WE pin on FlexROM_100
2020-11-11 minor touches
2020-11-23 FlexROM_100 & FlashROM_100 fix ALE/WE
2020-11-23 readme
2021-03-07 simpler programming adapters, update pics and BOMs
2021-03-11 add FlashROM_100_tsop
2021-03-15 0.3mm drills, gnd zone fills
2021-03-16 make room to stow programming jumper on 28C256_to_27C256
2021-05-09 Rename FlashROM_8300 to FLASH_23C1000
2021-05-18 add model 100 optrom programming adapter. readme and renders
2021-05-18 renders
2021-05-18 schematic plots
2021-10-17 add DS1000_DIP14
2022-09-11 kicad 6
2022-10-12 Fix wrong pinout on FlashROM_100 TSOPgit add -A!
2022-10-12 dual tsop footprint on flashrom_100
2022-10-12 render
2022-10-12 programming adapter board outline & ground pour
2022-10-12 programming adapter sch
2022-10-12 flashrom_100_plcc outline
2022-10-12 23C100 DIP28 outline, gnd, silk
2022-10-12 m100 optrom reader outline, silk, sch
2022-10-12 23C1000 silk, sch, gnd
2022-10-12 FlexROM_102 outline, sch
2022-10-13 various minor cleanups
2022-11-15 add FlexROM_200_M13
2022-12-01 flexrom 102 & 200 accept eeprom or fram
2023-02-23 flashrom_100 pin names & minor trace move
2023-06-16 dual-tsop footprint on flash_23c1000
2023-06-16 dual tsop footprint on flash_23c100_dip28
2023-07-05 23C1000: kicad 7, dual tsop footprint, teardrops
2023-07-05 23C1000 DIP-28 tsop-32 daul footprint & teardrops
2025-01-16 Update README.md
    Add OshPark PCB project and DigiKey cart
2025-02-10 add SM8 DIP8, readme

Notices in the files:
FlexROM_102.kicad_pcb:
CC-BY-SA
